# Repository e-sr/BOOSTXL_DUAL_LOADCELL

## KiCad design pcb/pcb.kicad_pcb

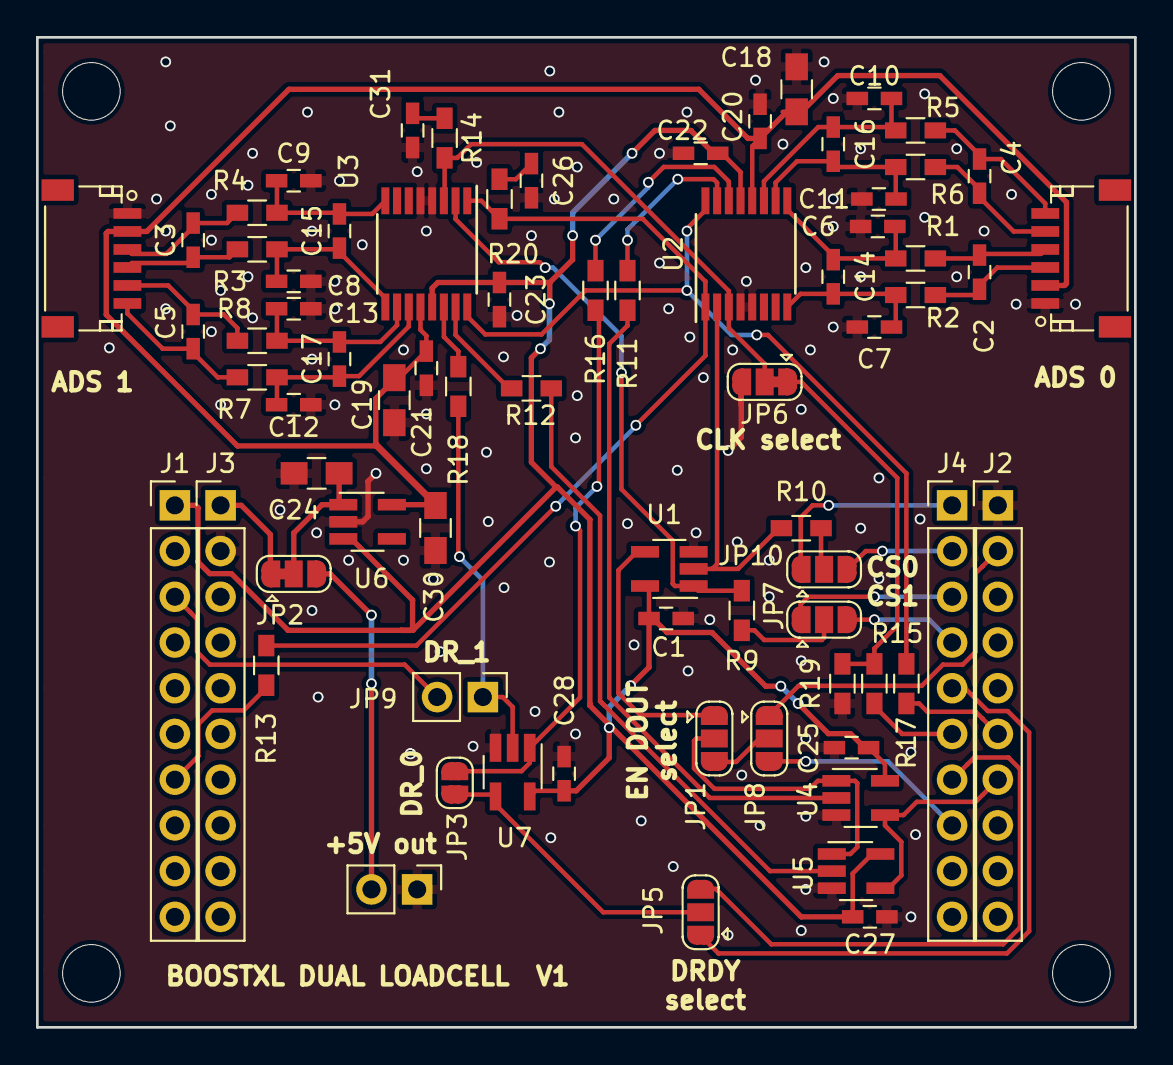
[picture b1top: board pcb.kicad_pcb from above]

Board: 2 copper layers, 61.0 x 55.0 mm, 77 parts (0 on the bottom side), 57 nets.

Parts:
C1, C20, C21, C22, C23, C25, C27, C28: 0.1u; C_0603_HandSoldering
C2, C3, C4, C5, C6, C7, C8, C9, C10, C11, C12, C13, C14, C15, C16, C17, C26, C31: C; C_0603_HandSoldering
C18, C19, C24, C30: 1u; C_0805_HandSoldering
H1, H2, H3, H4: MountingHole; MountingHole_3.2mm_M3_ISO7380
J1: TI_BOOSTER_40_J1; PinHeader_1x10_P2.54mm_Vertical
J2: TI_BOOSTER_40_J2; PinHeader_1x10_P2.54mm_Vertical
J3: TI_BOOSTER_40_J3; PinHeader_1x10_P2.54mm_Vertical
J4: TI_BOOSTER_40_J4; PinHeader_1x10_P2.54mm_Vertical
J5, J6: Conn_01x06; JST_SH_SM06B-SRSS-TB_06x1.00mm_Angled
J7: Conn_01x02; Socket_Strip_Straight_1x02_Pitch2.54mm
JP1, JP5, JP7, JP8, JP10: SolderJumper_3_Open; SolderJumper-3_P1.3mm_Open_RoundedPad1.0x1.5mm
JP2, JP6: SolderJumper_3_Bridged12; SolderJumper-3_P1.3mm_Bridged12_RoundedPad1.0x1.5mm
JP3: SolderJumper_2_Open; SolderJumper-2_P1.3mm_Open_RoundedPad1.0x1.5mm
JP9: SolderJumper_2_Open; Socket_Strip_Straight_1x02_Pitch2.54mm
R1, R2, R3, R4, R5, R6, R7, R8, R14, R20: R; R_0603_HandSoldering
R9, R10, R11, R12, R13, R15, R16, R17, R18: 47; R_0603_HandSoldering
R19: 10k; R_0603_HandSoldering
U1: 74LVC1G02; SOT-23-5_HandSoldering
U2, U3: ADS1220; TSSOP-16_4.4x5mm_Pitch0.65mm
U4, U5: SN74LVC1G125DBVR; SOT-23-5_HandSoldering
U6: LP5907MFX-3_3_NOPB; SOT-23-5_HandSoldering
U7: 74LVC1G32; SOT-23-5_HandSoldering

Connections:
+5V: J3.1, JP2.1
/AVDD: C18.1, C19.1, C20.1, C21.1, C30.1, J5.2, J6.2, U2.12, U3.12, U6.5
/CLK: JP6.2, R14.1, U2.3, U3.3
/CS_0: R10.2, U1.2, U2.2
/CS_1: R9.2, U1.1, U3.2
/DIN(SIMO): R17.2, U2.16, U3.16
/DOUT(SOMI): J2.7, U4.4, U5.4
/DOUT_0: R11.1, U4.2
/DOUT_1: R12.1, U5.2
/DR_0: JP3.1, R16.1, U7.1
/DR_1: JP9.1, R18.1, U7.2
/EN_DOUT: JP1.3, JP8.2
/EN_DOUT_: JP1.2, U4.1, U5.1
/SCLK: R13.2, R20.1, U2.1, U3.1
GND: C1.1, C6.1, C7.1, C8.1, C9.1, C10.1, C11.1, C12.1, C13.1, C18.2, C19.2, C20.2, C21.2, C22.1, C23.1, C24.2, C25.1, C26.2, C27.1, C28.1, C30.2, C31.2, J2.1, J3.2, J5.1, J6.1, J7.1, JP6.3, R19.1, U1.3, U2.4, U2.5, U3.4, U3.5, U4.3, U5.3, U6.2, U7.3
unnamed: C2.1, J5.4, R1.2
unnamed: C2.2, J5.3, R2.2
unnamed: C3.1, J6.4, R3.2
unnamed: C3.2, J6.3, R4.2
unnamed: C4.1, J5.6, R5.2
unnamed: C4.2, J5.5, R6.2
unnamed: C5.1, J6.6, R7.2
unnamed: C5.2, J6.5, R8.2
unnamed: C10.2, C16.1, R5.1, U2.11
unnamed: C11.2, C16.2, R6.1, U2.10
unnamed: C12.2, C17.1, R7.1, U3.11
unnamed: C13.2, C17.2, R8.1, U3.10
unnamed: C6.2, C14.1, R1.1, U2.9
unnamed: C7.2, C14.2, R2.1, U2.8
unnamed: C8.2, C15.1, R3.1, U3.9
unnamed: C9.2, C15.2, R4.1, U3.8
unnamed: C24.1, JP2.2, U6.1
unnamed: C26.1, R20.2
unnamed: C31.1, R14.2
unnamed: J1.3, JP9.2
unnamed: J1.7, R13.1
unnamed: J2.2, JP8.1
unnamed: J2.6, R17.1
unnamed: J4.1, JP10.1
unnamed: J4.2, JP10.3
unnamed: J4.3, JP7.1
unnamed: J4.4, JP7.3
unnamed: J4.5, JP5.1
unnamed: J4.6, R15.1
unnamed: J4.7, JP5.3
unnamed: J4.8, JP8.3
unnamed: J7.2, JP2.3
unnamed: JP1.1, U1.4
unnamed: JP3.2, JP5.2, U7.4
unnamed: JP6.1, R15.2, R19.2
unnamed: JP7.2, R9.1
unnamed: JP10.2, R10.1
unnamed: R11.2, U2.15
unnamed: R12.2, U3.15
unnamed: R16.2, U2.14
unnamed: R18.2, U3.14
VCC: C1.2, C22.2, C23.2, C25.2, C27.2, C28.2, J1.1, U1.5, U2.13, U3.13, U4.5, U5.5, U6.3, U7.5

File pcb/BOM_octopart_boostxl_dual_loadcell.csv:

Qty,Line Item,Manufacturer,MPN,Octopart URL,Schematic Reference,Internal Part Number,Description,Total Qty (@ Batch Size: 2),SKU,Packaging,Unit Price (@ Batch Size: 2),In Stock,MOQ,URL,Distributor [Lowest Price (Overall)],SKU [Lowest Price (Overall)],Packaging [Lowest Price (Overall)],Unit Price (@ Batch Size: 2) [Lowest Price (Overall)],Line Total [Lowest Price (Overall)],Batch Total [Lowest Price (Overall)],In Stock [Lowest Price (Overall)],MOQ [Lowest Price (Overall)],URL [Lowest Price (Overall)],Notes
,,,,,,,,,Digi-Key,Digi-Key,Digi-Key,Digi-Key,Digi-Key,Digi-Key,,,,,,,,,,
12,06033C104JAT2A,AVX,06033C104JAT2A,https://octopart.com/06033c104jat2a-avx-195750,"C1, C14, C15, C16, C17, C20, C21, C22, C23, C25, C27, C28",,0.1u,24,478-3713-1-ND,Cut Tape,0.27274307500000006,1511758,1,https://octopart.com/click/track?ak=39ac400e&sig=01cf9c5&sid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,Voyager Components,06033C104JAT2A,,0.09917930000000001,1.1901516,2.3803032,1298,,https://octopart.com/click/track?ak=39ac400e&sig=00a5bfe&sid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,
4,CGA3E1X7R1E105K080AD,TDK,CGA3E1X7R1E105K080AD,https://octopart.com/cga3e1x7r1e105k080ad-tdk-27956405,"C2, C3, C4, C5",,1u,8,445-9819-1-ND,Cut Tape,0.35704548,4387,1,https://octopart.com/click/track?ak=39ac400e&sig=0d94478&sid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,"Arrow Electronics, Inc.",CGA3E1X7R1E105K080AD,Cut Tape,0.27323897150000004,1.0929558860000002,2.1859117720000003,3003,1,https://octopart.com/click/track?ak=39ac400e&sig=0c270e4&sid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,
8,CC0603JRX7R9BB103,Yageo,CC0603JRX7R9BB103,https://octopart.com/cc0603jrx7r9bb103-yageo-9287396,"C6, C7, C8, C9, C10, C11, C12, C13",,0.01u,16,311-1778-1-ND,Cut Tape,0.075376268,92793,1,https://octopart.com/click/track?ak=39ac400e&sig=0daaad3&sid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,Mouser,CC0603JRX7R9BB103,,0.051573236,0.412585888,0.825171776,6106,1,https://octopart.com/click/track?ak=39ac400e&sig=003455d&sid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,
2,SM06B-SRSS-TB(LF)(SN),JST,SM06B-SRSS-TB(LF)(SN),https://octopart.com/sm06b-srss-tb%28lf%29%28sn%29-jst-289309,"J5, J6",,Conn_01x06,4,455-1806-1-ND,Cut Tape,0.82318819,86152,1,https://octopart.com/click/track?ak=39ac400e&sig=0d6f3ab&sid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,LCSC,C160405,,0.2922026738413028,0.5844053476826055,1.168810695365211,1308,1,https://octopart.com/click/track?ak=39ac400e&sig=0858c2a&sid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,
8,RC0603FR-071KL,Yageo,RC0603FR-071KL,https://octopart.com/rc0603fr-071kl-yageo-55402882,"R1, R2, R3, R4, R5, R6, R7, R8",,1k,16,311-1.00KHRCT-ND,Cut Tape,0.023803032000000002,58442705,1,https://octopart.com/click/track?ak=39ac400e&sig=0fe2519&sid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,"Arrow Electronics, Inc.",RC0603FR-071KL,Cut Tape,0.0013885102,0.0111080816,0.0222161632,72,1,https://octopart.com/click/track?ak=39ac400e&sig=0f08049&sid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,
9,CRCW060347R0JNEAHP,Vishay,CRCW060347R0JNEAHP,https://octopart.com/crcw060347r0jneahp-vishay-44383251,"R9, R10, R11, R12, R13, R15, R16, R17, R18",,47,18,541-47SACT-ND,Cut Tape,0.140834606,20000,1,https://octopart.com/click/track?ak=39ac400e&sig=0e1436c&sid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,element14 APAC,2904165,,0.05350180455528279,0.48151624099754514,0.9630324819950903,5000,1,https://octopart.com/click/track?ak=39ac400e&sig=0b57cbc&sid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,
1,SN74LVC1G02DBVR,Texas Instruments,SN74LVC1G02DBVR,https://octopart.com/sn74lvc1g02dbvr-texas+instruments-464409,U1,,74LVC1G02,2,296-11597-1-ND,Cut Tape,0.42647099,14866,1,https://octopart.com/click/track?ak=39ac400e&sig=04ffe57&sid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,Newark,76C4065,Cut Tape,0.055540408000000006,0.055540408000000006,0.11108081600000001,2760,1,https://octopart.com/click/track?ak=39ac400e&sig=076436f&sid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,
2,ADS1220IPWR,Texas Instruments,ADS1220IPWR,https://octopart.com/ads1220ipwr-texas+instruments-29520932,"U2, U3",,ADS1220,4,296-39851-1-ND,Cut Tape,8.45007636,5425,1,https://octopart.com/click/track?ak=39ac400e&sig=0ecd862&sid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,LCSC,C48263,,4.111659651811449,8.223319303622898,16.446638607245795,1055,1,https://octopart.com/click/track?ak=39ac400e&sig=07b4c9b&sid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,
2,SN74LVC1G125DBVR,Texas Instruments,SN74LVC1G125DBVR,https://octopart.com/sn74lvc1g125dbvr-texas+instruments-464431,"U4, U5",,SN74LVC1G125DBVR,4,296-11603-1-ND,Cut Tape,0.35704548,70827,1,https://octopart.com/click/track?ak=39ac400e&sig=0e1766e&sid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,Rochester Electronics,SN74LVC1G125DBVR,,0.09917930000000001,0.19835860000000002,0.39671720000000005,163270,,https://octopart.com/click/track?ak=39ac400e&sig=03302c3&sid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,
1,LP5907MFX-4.5/NOPB,Texas Instruments,LP5907MFX-4.5/NOPB,https://octopart.com/lp5907mfx-4.5%2Fnopb-texas+instruments-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,U6,,LP5907MFX-4.5/NOPB,2,296-39064-1-ND,Cut Tape,0.5454861500000001,40605,1,https://octopart.com/click/track?ak=39ac400e&sig=061f0af&sid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,TI store,LP5907MFX-4.5/NOPB,Cut Tape,0.43638892,0.43638892,0.87277784,6908,1,https://octopart.com/click/track?ak=39ac400e&sig=053d04c&sid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,
1,SN74LVC1G32DBVR,Texas Instruments,SN74LVC1G32DBVR,https://octopart.com/sn74lvc1g32dbvr-texas+instruments-465562,U7,,74LVC1G32,2,296-9847-1-ND,Cut Tape,0.35704548,136989,1,https://octopart.com/click/track?ak=39ac400e&sig=09dac67&sid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,Rochester Electronics,SN74LVC1G32DBVR,,0.09917930000000001,0.09917930000000001,0.19835860000000002,24499,,https://octopart.com/click/track?ak=39ac400e&sig=0866481&sid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,

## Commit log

2019-01-28 ADS1220 object implementation
    ads1220_t type defined which contains methods to write and read to the device and buffers containing read and written registers
    Change made because we want use the library in case of many devices on a spi bus or on the case of many devices on differnt spi bus
    Device specific code is outside the library
2019-02-04 ADS1220 src typedef using stdint.h
    used typedf of stdint.h
2019-02-04 BXL_D_LC is now working on f28069
2019-02-04 Added CLOCK calculations notebook
    Calculaate the external clock freq (PWM) to ADS1220 to have precise SR.
2019-02-05 added offset and calibration to ads1220 object
    implemented calibration and offset calculation within object and methods
